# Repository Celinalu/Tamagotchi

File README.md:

# Tamagotchi
This Tamagotchi is a digital pet that you can raise. It runs off an Xiao Esp32C3 board and has an OLED board that displays the pet's condition at all times, to remind people of the mood of their pet. I added LED lights that correspond to different moods (sad, happy, and neutral).

# How it's made:
Programs used: KiCad, Fusion, Arduino IDE
I first created the schematic and the PCB using KiCad. I took a lot of inspiration from the guide on the Tamagochi made in the Fallout tutorial. So I used the same processor, which is the XIAO Esp32C3 board. I connected everything to the corresponding parts after looking at the datasheet. This part won't take you very long, especially if you have a bit of experience. The wiring for PCB is quite nice in the sense that since there are not a lot of parts, wiring is not much of a hassle. I did add a ground layer on the front side. For my battery, I added a lithium battery that is outside of the PCB. 

For my case, I went with a pretty simple design since it is my first time making a 3D model. To secure the PCB, I used the holes that the OLED screen has to secure the PCB to the back of the case. Then I also added holes in the sides of the case that make it so that the front and back are connected and won't fall apart. I did threads for the holes except the one for the battery, since the hole was too small. I also added an opening for my usbc charging port as well as the LEDs and the  buttons, which I just used the extrude button to cut.  

For the firmware, I learned a lot from the guide in Fallout since I never used C++ before. I did most of what was suggested to do in the guide, so I would suggest that as the starting point. The main part, I think, is connecting the different parts of the hardware to the software as long the connection is there the rest will go pretty smoothly. For the LEDs, I kept it pretty simple with just one LED corresponding to each mood; I kept it to three. So when a mood change is detected, a new LED light will light up.

# How to use it:
When you connect the Tamagotchi to the USBC cable, it will turn on and show the "Tamagotchi loading..." on the OLED screen for 1 second before your pet starts with it's hunger, happiness, and energy at 80/100. Then every 5 seconds all the stats will drop by 1, so if you leave it alone for too long it will eventally die WHICH YOU DONT WANT. So to avoid that, the three buttons that you can press: left for feed (hunger +10), middle for play (happiness +10 energy -5), right for sleep (energy +15). Buttons have a 200ms debounce time, so double presses are ignored. 

The pet's face and the LEDs also change based on mood:
Happy face and green LED = all stats above 50
Neutral face and yellow LED = stats are between 50 and 30
Sad face and red LED = stats under 30

# Why I made this:
I wanted to challenge myself to do something out of my comfort zone. This project required many different parts combined, so I thought it was a very good learning opportunity to use many different things combined (3d modeling, hardware, and software). I think the project is also very fun, and you can really personalize the end product to whatever you like. This project had many complex parts, but they are small enough that it won't take a massive amount of time. I also wanted to learn how to incorporate an OLED screen in my build, so this was also my other reason for creating this.  

# Zine Page

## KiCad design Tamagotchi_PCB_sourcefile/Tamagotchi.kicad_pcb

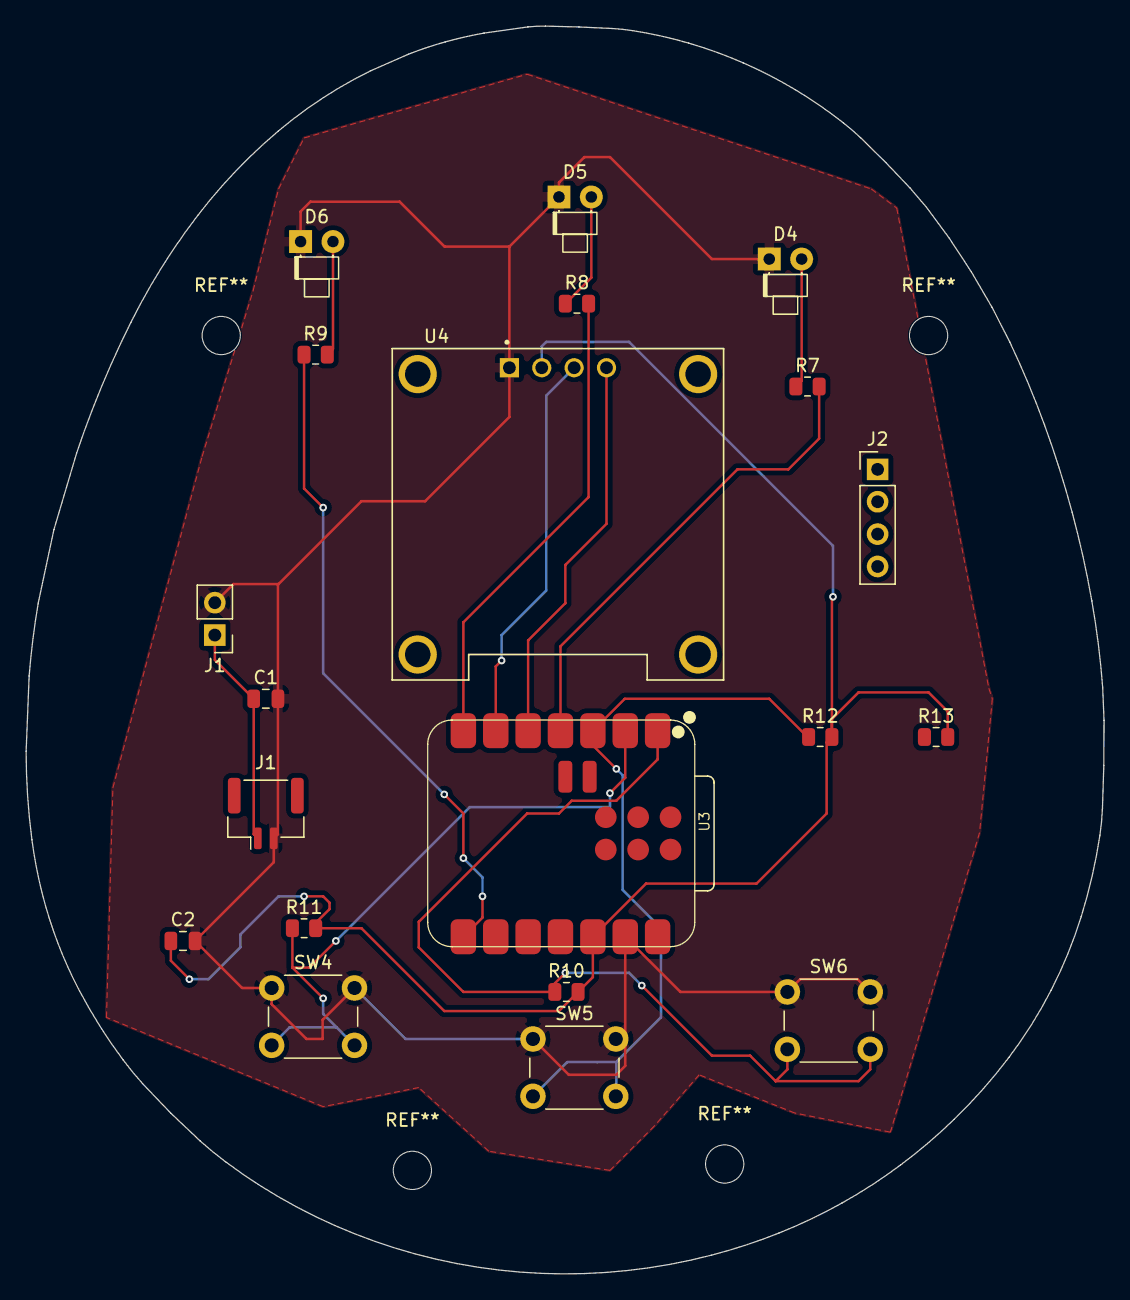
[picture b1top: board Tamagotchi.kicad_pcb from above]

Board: 2 copper layers, 84.6 x 97.9 mm, 20 parts (0 on the bottom side), 14 nets.

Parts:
C1: C_Polarized; C_0805_2012Metric
C2: 0.1uF; C_0805_2012Metric
D4, D5, D6: LED; LED_D1.8mm_W1.8mm_H2.4mm_Horizontal_O1.27mm_Z1.6mm
J1: Battery connector; PinHeader_1x02_P2.54mm_Vertical
J1#2: Battery connector; JST_GH_BM02B-GHS-TBT_1x02-1MP_P1.25mm_Vertical
J2: Programing; PinHeader_1x04_P2.54mm_Vertical
R7, R8, R9: 1K; R_0805_2012Metric
R10: 10K; R_0805_2012Metric
R11, R12, R13: 10k; R_0805_2012Metric
SW4, SW5, SW6: SW_Push; SW_PUSH_6mm_H5mm
U3: XIAO-ESP32-C3-SMD
U4: DM-OLED096-636; MODULE_DM-OLED096-636

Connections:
+3V3: C2.1, R10.2, R11.2, R12.2, R13.2, U3.12 (3V3), U4.2 (VCC_IN)
GND: C1.2, C2.2, D4.1 (K), D5.1 (K), D6.1 (K), J1.2, J1#2.2, SW4.1, SW5.1, SW6.1, U3.13 (GND), U4.1 (GND)
unnamed: D4.2 (A), R7.1
unnamed: D5.2 (A), R8.1
unnamed: D6.2 (A), R9.2
unnamed: C1.1, J1.1, J1#2.1
unnamed: R10.1, SW6.2, U3.1 (GPIO2_A0_D0)
unnamed: R11.1, SW4.2, U3.2 (GPIO3_A1_D1)
unnamed: R12.1, SW5.2, U3.3 (GPIO4_A2_D2)
unnamed: R7.2, U3.4 (GPIO5_A3_D3)
unnamed: U3.5 (GPIO6_D4_SDA), U4.4 (SDA)
unnamed: U3.6 (GPIO7_D5_SCL), U4.3 (SCL)
unnamed: R9.1, U3.8 (GPIO20_D7_RX)
unnamed: R8.2, U3.7 (GPIO21_D6_TX)

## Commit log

2026-04-11 barely did anything
    actually cant download the part
2026-04-11 finally found a oled
2026-04-12 finished the schematic
2026-04-12 trying to fix my errors in schematic
2026-04-13 spend so much time finding footprints
2026-04-17 commiting this for now cuz my kicad is tweaking
2026-04-17 did my pcb I guess some slik screen errors idk how to fix rn
2026-04-18 added some resistor and capacitors
2026-04-18 Done pcb!!!
2026-04-19 made sme step file to use for the case modeling
2026-04-24 finished 3d model
2026-04-24 testing out if my github deskstop still functions
2026-04-25 Delete Tamagochi_code.ino
    had two of the same thing
2026-04-25 starting readme
    Added description of the Tamagotchi project including hardware details and mood indicators.
2026-04-25 think I explained almost everything..
    Expanded the README to include details on the creation process, usage instructions, and motivations behind the Tamagotchi project.
2026-04-26 trying to do final checks on everything as well as finishing writing the readme
2026-04-26 just updating stuff
2026-05-08 had to rewire pcb due to changing the esp32
2026-05-08 need to rework so muchhh
2026-05-08 have so much to fixxx
2026-05-08 just saving some things last min
2026-05-09 finally figured out battery
2026-05-18 added and delated stuff
2026-05-18 edited the readme to what I have currently
    Updated descriptions and images for the Tamagotchi project in README.md.
2026-05-18 edited photo of zine
2026-06-01 updated cuz I forgot power source
2026-06-04 Update README with additional images
    Added two new images showcasing the Tamagotchi case and PCB.
2026-06-04 Update README with new Zine Page image
    Added a new image to the Zine Page section.
